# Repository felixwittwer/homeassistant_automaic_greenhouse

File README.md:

&nbsp; &nbsp; 

<br>

<br>

# homeassistant_automaic_greenhouse
A cool Project to make your greenhouse smart. What about automaic irrigation and collecting enviromental data right from your garden.

## About the project
This project actually is sthe second iteration on me trying to automate our greenhouse. The first version relied on an Arduino Uno powered by a 24V powertool battery and sensordata was logged to an SD-card. Since we now have power and wifi connectivity to the greenhouse I wanted to step up the game and build something that is way smarter and will hopefully last forever. If you were wondering this is why an industrial grade electrical box with rails was used.

## The concept of sensor and action modules
This project is a very specked out version of a greenhouse automation and environmental monitoring system. Due to cost or other reasons you might not include all the sensors used by me. To make it easyer to do so each sensor is getting his own folder inside the sensor modules directory. You will find everything you need to know about a so called sensor module inside this folder from CAD files, STL Files for 3D printing and scematics to instructions on sourcing the parts.

A detailed list of all sensors used in the project can be found in the [**sensor modules**](/sensor%20modules/) directory.

Like the sensors you might choose to leave out some action modules aka the parts that actually do something like the relais and solanoids for an irrigation system.

These so called action modules with all their corresponding documentation and files can be found in the [**action modules**](/action%20modules/) directory.

## Where to start

If you are completly new to this project you might take a look at the folowing map. Go thrugh the individual questions and build your own Green Assistant. Follow the link below to get to an interactive pdf version. Clicking on the links will be more func than searching in this Repo.

<!--  -->

## The project

A list of all uesd parts can be found in the **parts** directory.

All files corresponding to the main part of the project so the electrical box with all the controll electronics can be found in the **core** directory.

### Mounting hardware

### Irrigation system

### PCB

You will need this PCB to connect all sensors reliably to the ESP32 S3. All unused pins of the ESP also have a connection to a pinheader so feel free to add sensors without needing to modify the PCB. 

PCB Sourcefiles can be found inside [core/esp32 pcb and mounting/pcb files/esp shield](./core/esp32%20pcb%20and%20mounting/pcb%20files/esp_shield/).

### Wiring

When you have choosen your parts and want to build your Green Assistant have alook at this wiring diagramm of all the sensors.

### Homeassistant Configuration and Dashboards

All stuff regarding Homeassistant can be found in the **homeassistant files** directory. Dashboards will be in a seperate folder.

<br>

### Project Video

https://youtu.be/dZTHF3ozego

# BOM

**@Hackclub** please note that some parts are a bit expensive but I already have them so they are listed here just for reference if somebody wontas to build his own Green Assistant. Go [here](./parts/Hackclub_BOM.csv) for a list of parts I seek Hackclub sponsorship for.

**sum: 318.49 USD**

**hopefully paid for by Hackclub :): 81.47 USD**

| part name       | amount     | price | link | note |
| --------------- | ---------- | ----- | ---- | ---  |
| 4 in 1 solanoid 12V DC | 1          | 17.46 USD | https://de.aliexpress.com/item/1005003222372894.html?spm=a2g0o.productlist.main.2.7b883b2805U1oZ&algo_pvid=367fdcb6-b2b8-4472-b90f-06dec834dcc7&pdp_ext_f=%7B%22order%22%3A%2290%22%2C%22eval%22%3A%221%22%7D&utparam-url=scene%3Asearch%7Cquery_from%3A
| 25m tubing 10mm inner diameter       | 1          | 26.92 USD   |https://de.aliexpress.com/item/1005006851012150.html?spm=a2g0o.productlist.main.7.4fc6qemXqemXUn&algo_pvid=38c16ebb-f0d1-407d-8d17-a22a1c15e6e7&pdp_ext_f=%7B%22order%22%3A%224%22%2C%22eval%22%3A%221%22%7D&utparam-url=scene%3Asearch%7Cquery_from%3A|
| Relais modul 4 Way | 1 | 1.19 USD | https://de.aliexpress.com/item/1005002867727977.html?spm=a2g0o.productlist.main.11.13a1dJEvdJEvMc&algo_pvid=4fdea743-d29c-430b-87f1-e4d68f1caa09&pdp_ext_f=%7B%22order%22%3A%222771%22%2C%22eval%22%3A%221%22%7D&utparam-url=scene%3Asearch%7Cquery_from%3A
| Electrical box | 1 | 127.75 USD| https://www.elektro4000.de/Elektroinstallations-Systeme/Installationsverteiler/Leergehaeuse/Eaton-Unterkasten-U-CI44E::55531.html |any box or mounting with DIN Rails will be fine |
| Electrical Box Lid | 1 | 82.50 USD | https://www.elektro4000.de/Installationsmaterial/Verbindungsmaterial/Deckel/Gehaeuse-fuer-Montage-auf-der-Wand/Eaton-CI-Gehaeuse-Deckel-D125-CI44::55551.html
| DIN Rail Powersuply 5V DC Out 15W | 1 | 1.19 USD | https://de.aliexpress.com/item/1005006112378832.html?spm=a2g0o.productlist.main.1.c7272b87z7yuLe&algo_pvid=7effdf59-b7f3-46b6-8a67-f866ad0ae34e&pdp_ext_f=%7B%22order%22%3A%221440%22%2C%22eval%22%3A%221%22%7D&utparam-url=scene%3Asearch%7Cquery_from%3A
| DIN Rail Powersuply 12V DC Out 15W | 1 | 1.19 USD | https://de.aliexpress.com/item/1005006112378832.html?spm=a2g0o.productlist.main.1.c7272b87z7yuLe&algo_pvid=7effdf59-b7f3-46b6-8a67-f866ad0ae34e&pdp_ext_f=%7B%22order%22%3A%221440%22%2C%22eval%22%3A%221%22%7D&utparam-url=scene%3Asearch%7Cquery_from%3A
| ESP32-S3 | 1 | 1.19 USD | https://de.aliexpress.com/item/1005005051294262.html?spm=a2g0o.productlist.main.1.44e77227eWXK8y&algo_pvid=8d3c9e27-0ba9-47e2-ad79-140c2bfeddc5&pdp_ext_f=%7B%22order%22%3A%223124%22%2C%22eval%22%3A%221%22%7D&utparam-url=scene%3Asearch%7Cquery_from%3A | |
| BH1750 Breakout | 1          | ~0.73 USD      | https://de.aliexpress.com/item/1005007347385714.html?spm=a2g0o.productlist.main.6.777f1c59hsCKIx&algo_pvid=ace7ffce-6eb3-4c41-b141-61d0790658f1&pdp_ext_f=%7B%22order%22%3A%223%22%2C%22eval%22%3A%221%22%7D&utparam-url=scene%3Asearch%7Cquery_from%3A&gatewayAdapt=glo2deu  | |
| DHT22           | 1          | ~0.94 USD      | https://de.aliexpress.com/item/1005006963999579.html?spm=a2g0o.productlist.main.8.4fe01vBx1vBxc6&aem_p4p_detail=202506230828074971261634829080000442240&algo_pvid=fcda431a-64bc-4580-a176-f59294651d79&pdp_ext_f=%7B%22order%22%3A%2248%22%2C%22eval%22%3A%221%22%7D&utparam-url=scene%3Asearch%7Cquery_from%3A&search_p4p_id=202506230828074971261634829080000442240_2  | ---             |
| DS18B20 2 meter cable | 1          | ~1.17 USD      | https://de.aliexpress.com/item/1005008024174225.html?spm=a2g0o.productlist.main.2.892a1a0e74KpG7&algo_pvid=fdca3388-9d61-4050-a1fa-ad9c645db0ba&pdp_ext_f=%7B%22order%22%3A%221023%22%2C%22eval%22%3A%221%22%7D&utparam-url=scene%3Asearch%7Cquery_from%3A  | ---             |
| MH-Z19B | 1          | ~21.68 USD      | https://de.aliexpress.com/item/4001296615950.html?spm=a2g0o.productlist.main.1.10df56e9kDzAiu&algo_pvid=496ed4bc-a93e-4799-9a9a-8ecbef09edf5&pdp_ext_f=%7B%22order%22%3A%2296%22%2C%22eval%22%3A%221%22%7D&utparam-url=scene%3Asearch%7Cquery_from%3A  | ---             |
| Capaciative Soil Moisture Sensor | 5          | ~2.37 USD (5pcs)      | https://de.aliexpress.com/item/1005005202930632.html?spm=a2g0o.productlist.main.1.48797dceO9blZE&algo_pvid=bb3dd897-6049-4f43-8d40-2504b2c600fa&pdp_ext_f=%7B%22order%22%3A%222164%22%2C%22eval%22%3A%221%22%7D&utparam-url=scene%3Asearch%7Cquery_from%3A  | ---             |
| Shrink tubing 4:1 24mmx1.22 meter | 1          | ~3.08 USD             | https://de.aliexpress.com/item/32812574636.html?spm=a2g0o.productlist.main.1.1d6b2ff5rBIF75&algo_pvid=04fab651-0aed-4642-95ae-c8c0465ccd88&pdp_ext_f=%7B%22order%22%3A%221827%22%2C%22eval%22%3A%221%22%7D&utparam-url=scene%3Asearch%7Cquery_from%3A  | ---             |
| Reed switch Breackout | 1          | ~0.65 USD (10pcs)      | https://de.aliexpress.com/item/1005008372135180.html?spm=a2g0o.productlist.main.19.4fe959f0QsmFeq&algo_pvid=b2bcd3b2-6353-4def-9e17-8f16d86e7c01&pdp_ext_f=%7B%22order%22%3A%2245%22%2C%22eval%22%3A%221%22%7D&utparam-url=scene%3Asearch%7Cquery_from%3A  | ---             |
| magnet 10x2mm   | 2          | ~2.26 USD (20pcs)              | https://de.aliexpress.com/item/1005009266299777.html?spm=a2g0o.productlist.main.1.73353687XlFb9S&algo_pvid=005b8154-ff95-40c2-aa0e-3425ebdeabd9&pdp_ext_f=%7B%22order%22%3A%2242%22%2C%22eval%22%3A%221%22%7D&utparam-url=scene%3Asearch%7Cquery_from%3A  | ---             |
| PCB (without assembly) | 1 | ~5 USD subject to JLCPCB | | if you choose assembly it will be more expensive but I already have the parts at home |
| M3 screws 10mm  | 8          | ~              |   | ---             |
| M3 screws 15mm  | 2          | ~              |   | ---             |
| M3 nuts         | 10          | ~              |   | ---             |
| -> set of screws and nuts | 1| 1.19 USD | https://de.aliexpress.com/item/1005007273134914.html?spm=a2g0o.productlist.main.7.2cb11b1aQ6xTNZ&algo_pvid=134ed8c9-ae6d-44f4-80cc-761426203be1&pdp_ext_f=%7B%22order%22%3A%22476%22%2C%22eval%22%3A%221%22%7D&utparam-url=scene%3Asearch%7Cquery_from%3A
| some wire (15m)       | 2          | 21.22 USD              | https://de.aliexpress.com/item/1005007371239057.html?spm=a2g0o.productlist.main.8.a56f4f561YvSN9&aem_p4p_detail=2025063002162114202903362944350000136812&algo_pvid=5b7d4cc4-4e18-49cf-aad0-bd6d2e445630&pdp_ext_f=%7B%22order%22%3A%225%22%2C%22eval%22%3A%221%22%7D&utparam-url=scene%3Asearch%7Cquery_from%3A&search_p4p_id=2025063002162114202903362944350000136812_2  | ethernet cable is shielded -> better for analog sensors (especially for longer distances)            |
| t-piece         | 22         | ---   || 3D-printed part |
| nozzle-piece    | 22         | ---   || 3D-printed part |
| end-piece       | 4          | ---   || 3D-printed part |
| Ralais module mounting         | 1         | ---   || 3D-printed part |
| PCB Mounting | 1 | --- || 3D-printed part | 
| BH1750 case top        | 1          | ---            |   | 3D-printed part      |
| BH1750 case bottom     | 1          | ---            |   | 3D-printed part      |
| MH-Z19B case top        | 1          | ---            |   | 3D-printed part      |
| MH-Z19B case bottom     | 1          | ---            |   | 3D-printed part      |
| magnet case top        | 1          | ---            |   | 3D-printed part      |
| magnet case bottom     | 1          | ---            |   | 3D-printed part      |
| reed case top        | 1          | ---            |   | 3D-printed part      |
| reed case bottom     | 1          | ---            |   | 3D-printed part      |

**sum: 318.49 USD**

**hopefully paid for by Hackclub :) : 81.47 USD** 

# LICENSE
This work is licensed under CC BY-NC-SA 4.0. 

To view a copy of this license, visit https://creativecommons.org/licenses/by-nc-sa/4.0/

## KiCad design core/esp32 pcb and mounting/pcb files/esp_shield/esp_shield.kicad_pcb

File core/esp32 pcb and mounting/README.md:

# PCB Shield

This folder contains everything regarding the PCB. Furthermore there will be mounting hardware for DIN Rails in the mounting folder.

## PCB Production/Assembly

I recoment only getting the PCB manufactured and then poppulating the board yourself. There are not SMD parts on the PCB so assembly isn't as cheap as you are probably used to. Due to it's non smd nature sodering should be easy and replacing parts (maybe because they corrode in you greenhouse) is very simple and easy to pull of.

<br>

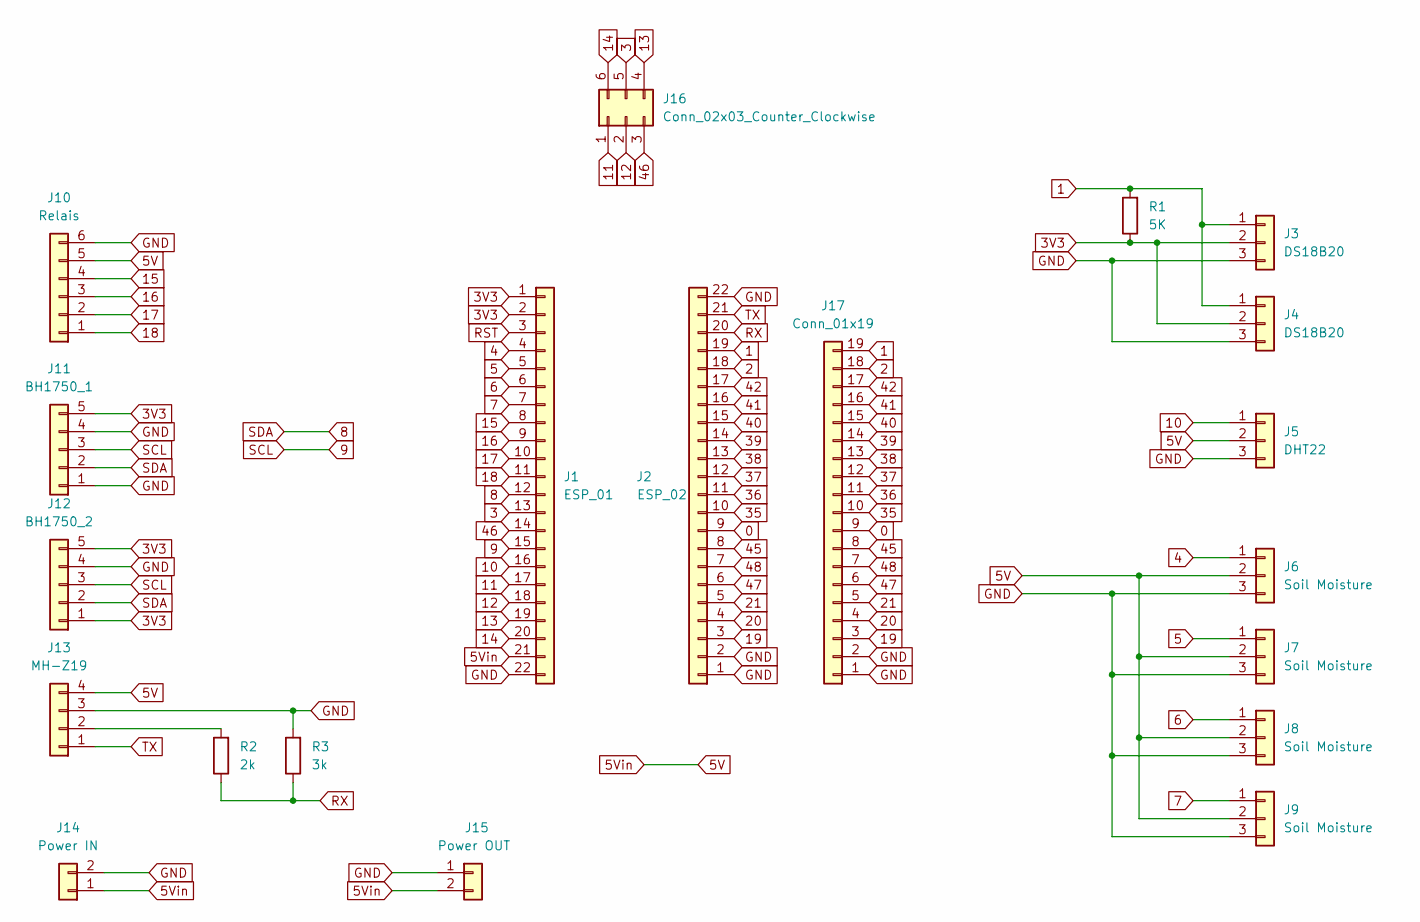
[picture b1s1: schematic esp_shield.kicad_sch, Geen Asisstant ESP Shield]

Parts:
J1: ESP_01; PinSocket_1x22_P2.54mm_Vertical
J2: ESP_02; PinSocket_1x22_P2.54mm_Vertical
J3, J4: DS18B20; TerminalBlock_Phoenix_MKDS-1,5-3-5.08_1x03_P5.08mm_Horizont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
J5: DHT22; TerminalBlock_Phoenix_MKDS-1,5-3-5.08_1x03_P5.08mm_Horizont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
J6, J7, J8, J9: Soil Moisture; TerminalBlock_Phoenix_MKDS-1,5-3-5.08_1x03_P5.08mm_Horizont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
J10: Relais; TerminalBlock_Phoenix_MKDS-1,5-6_1x06_P5.00mm_Horizontal
J11: BH1750_1; TerminalBlock_Phoenix_MKDS-1,5-5_1x05_P5.00mm_Horizontal
J12: BH1750_2; TerminalBlock_Phoenix_MKDS-1,5-5_1x05_P5.00mm_Horizontal
J13: MH-Z19; TerminalBlock_Phoenix_MKDS-1,5-4_1x04_P5.00mm_Horizontal
J14: Power IN; TerminalBlock_Phoenix_MKDS-1,5-2_1x02_P5.00mm_Horizontal
J15: Power OUT; TerminalBlock_Phoenix_MKDS-1,5-2_1x02_P5.00mm_Horizontal
J16: Conn_02x03_Counter_Clockwise; PinHeader_2x03_P2.54mm_Vertical
J17: Conn_01x19; PinHeader_1x19_P2.54mm_Vertical
R1: 5K; R_Axial_DIN0207_L6.3mm_D2.5mm_P10.16mm_Horizontal
R2: 2k; R_Axial_DIN0207_L6.3mm_D2.5mm_P10.16mm_Horizontal
R3: 3k; R_Axial_DIN0207_L6.3mm_D2.5mm_P10.16mm_Horizontal

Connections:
0: J2.9, J17.9
1: J2.19, J3.1, J4.1, J17.19, R1.2
2: J2.18, J17.18
3: J1.13, J16.5
3V3: J1.1, J1.2, J3.2, J4.2, J11.5, J12.1, J12.5, R1.1
4: J1.4, J6.1
5: J1.5, J7.1
5V: J1.21, J5.2, J6.2, J7.2, J8.2, J9.2, J10.5, J13.4, J14.1, J15.2
6: J1.6, J8.1
7: J1.7, J9.1
8: J1.12, J11.2, J12.2
9: J1.15, J11.3, J12.3
10: J1.16, J5.1
11: J1.17, J16.1
12: J1.18, J16.2
13: J1.19, J16.4
14: J1.20, J16.6
15: J1.8, J10.4
16: J1.9, J10.3
17: J1.10, J10.2
18: J1.11, J10.1
19: J2.3, J17.3
20: J2.4, J17.4
21: J2.5, J17.5
35: J2.10, J17.10
36: J2.11, J17.11
37: J2.12, J17.12
38: J2.13, J17.13
39: J2.14, J17.14
40: J2.15, J17.15
41: J2.16, J17.16
42: J2.17, J17.17
45: J2.8, J17.8
46: J1.14, J16.3
47: J2.6, J17.6
48: J2.7, J17.7
GND: J1.22, J2.1, J2.2, J2.22, J3.3, J4.3, J5.3, J6.3, J7.3, J8.3, J9.3, J10.6, J11.1, J11.4, J12.4, J13.3, J14.2, J15.1, J17.1, J17.2, R3.2
unnamed: J13.2, R2.2
RST: J1.3
RX: J2.20, R2.1, R3.1
TX: J2.21, J13.1

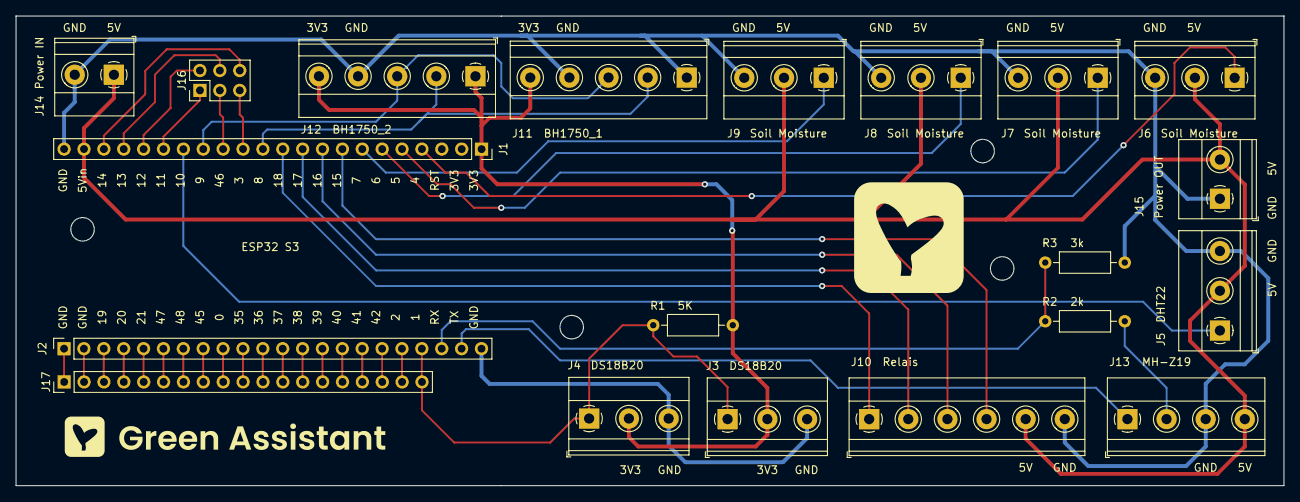
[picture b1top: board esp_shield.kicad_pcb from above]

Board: 2 copper layers, 162.0 x 60.0 mm, 20 parts (0 on the bottom side), 40 nets.

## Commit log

2025-05-24 Update README.md
    Add Badges
2025-05-29 adding journal files
2025-05-29 Update JOURNAL.md
    Add images for 03-30
2025-05-29 Update README.md
    Add ESPHome Badge
2025-05-30 creating project structure and adding LICENSE
2025-05-30 add core electrical box
2025-05-30 adding render of electrical box and sub README
2025-05-30 add more sub README files
2025-05-30 add window contacts
2025-05-30 adding relais board inside action modules
2025-06-05 adding branding and ds18b20 sensor module
2025-06-23 add bh1750 light sensor module
2025-06-23 improfing sensor moduel READMEs
2025-06-23 adding MH-Z19B sensor module
2025-06-23 add DHT22 sensor module
2025-06-23 add soil moisture sensor module
2025-06-23 finishing off sensor modules
2025-06-24 setting up Homeassistant and some prototyping
2025-06-24 adding Esphome config and Homeassistant dashboards
2025-06-24 adding esp32 pcb shield
2025-06-24 adding mount for pcb
2025-06-25 adding mounting for relais
2025-06-25 add irrigation system module
2025-06-25 add new electrical box and wiring diagram
2025-06-25 add some documentation
2025-06-30 adding BOM
2025-06-30 making some final touches before submission - finishing ESPHome config - fixing some typos
2025-06-30 fixing some typos in the main README
2025-06-30 making BOM readable for GitHub
2025-07-01 renaming folders for Hackclub
2025-07-03 fix image paths inside README
2025-07-17 add cable clips
2025-07-18 assemble pcb
2025-07-18 add M3 nut adapter
2025-07-19 add testing wiring to JOURNAL
2025-07-21 start wiring
2025-07-22 finish wiring + a small change on the pcb + start adding manual
2025-07-22 fix images in main README
2025-07-23 install electrical box
2025-07-25 installing irrigation sytsem
2025-07-25 installing more sensors inside the greenhouse
2025-07-26 add some images
2025-07-26 adding some images for journal
2025-07-26 add more configuration for irrigation system - watering routine - helpers for manual watering - register buildin LED
2025-08-06 add new version of door and window sensors
2025-08-13 add IRL image to README
